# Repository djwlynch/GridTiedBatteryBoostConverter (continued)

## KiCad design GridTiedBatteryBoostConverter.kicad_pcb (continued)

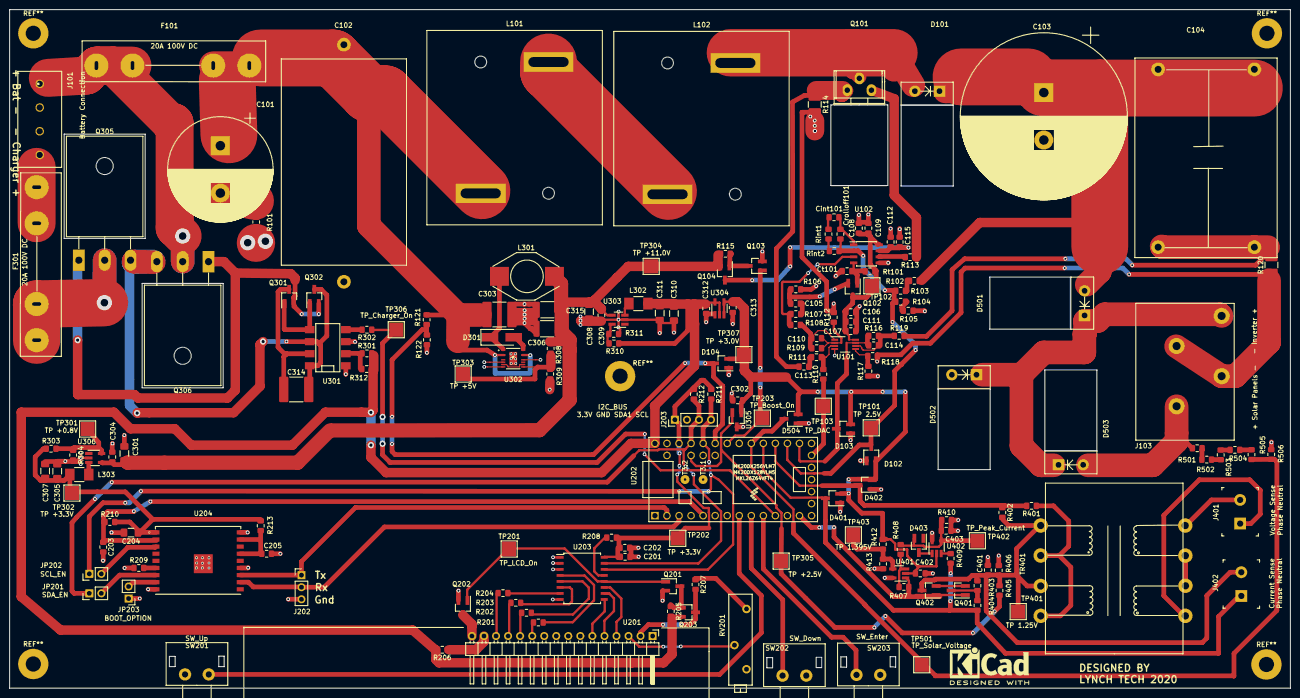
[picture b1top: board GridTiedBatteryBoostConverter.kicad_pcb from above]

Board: 2 copper layers, 270.1 x 143.1 mm, 183 parts (0 on the bottom side), 111 nets.

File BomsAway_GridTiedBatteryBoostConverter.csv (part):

Refs,Value,Footprint,Quantity,MFR,MPN,SPR,SPN
SW202,SW_Down,Buttons_Switches_ThroughHole_jl:SW_Tactile_SPST_Angled_FSM104,1,TE Connectivity ALCOSWITCH Switches,FSM104,digikey,450-1127-ND
SW203,SW_Enter,Buttons_Switches_ThroughHole_jl:SW_Tactile_SPST_Angled_FSM104,1,TE Connectivity ALCOSWITCH Switches,FSM104,digikey,450-1127-ND
SW201,SW_Up,Buttons_Switches_ThroughHole_jl:SW_Tactile_SPST_Angled_FSM104,1,TE Connectivity ALCOSWITCH Switches,FSM104,digikey,450-1127-ND
C402;C403;C309;C312;C304;C109;C112;C107;C202;C203;C205,0.1uF X7R 25V 10%,Capacitor_SMD:C_0805_2012Metric_Pad1.15x1.40mm_HandSolder,11,Samsung,CL21B104KACNNNC,digikey,1276-1099-1-ND
C302,0.47uF X7R 25V 10%,Capacitor_SMD:C_0805_2012Metric_Pad1.15x1.40mm_HandSolder,1,Samsung Electro-Mechanics,CL21B474KAFNNNE,digikey,1276-1074-1-ND
Cint101,0.56uF X7R 16V 10%,Capacitor_SMD:C_0805_2012Metric_Pad1.15x1.40mm_HandSolder,1,KEMET,C0805C564K4RACTU,dikikey,399-10074-1-ND
C105,100pF,Capacitor_SMD:C_0805_2012Metric_Pad1.15x1.40mm_HandSolder,1,KEMET,C0805C101JAGAC7800,digikey,399-15000-1-ND
C113,1nF,Capacitor_SMD:C_0805_2012Metric_Pad1.15x1.40mm_HandSolder,1,Yageo,CC0805KRX7R9BB102,digikey,311-1127-1-ND
C401;C313;C108;C114;C111;C106;C115;C201,1uF X7R 25V 10%,Capacitor_SMD:C_0805_2012Metric_Pad1.15x1.40mm_HandSolder,8,Wurth Elektronik,885012207078,digikey,732-7672-1-ND
Ct101,200pF C0G 2%,Capacitor_SMD:C_0805_2012Metric_Pad1.15x1.40mm_HandSolder,1,AVX Corporation,08051A201GAT2A,digikey,478-10384-1-ND
Crolloff101,68pF C0G 5%,Capacitor_SMD:C_0805_2012Metric_Pad1.15x1.40mm_HandSolder,1,Wurth Elektronik,885012007081,digikey,732-12227-1-ND
C110,6pF C0G,Capacitor_SMD:C_0805_2012Metric_Pad1.15x1.40mm_HandSolder,1,Yageo,CC0805CRNPO9BN6R0,digikey,311-4149-1-ND
C311;C310;C308;C307;C305;C301;C204,10uF X7R 25V 10%,Capacitor_SMD:C_1206_3216Metric_Pad1.42x1.75mm_HandSolder,7,Samsung Electro-Mechanics,CL31B106KAHNNNE,digikey,1276-1804-1-ND
C306;C315,33uF X7R 16V 20%,Capacitor_SMD:C_1812_4532Metric_Pad1.30x3.40mm_HandSolder,2,TDK Corporation,C4532X7R1C336M250KC,digikey,445-3924-1-ND
C303;C314,1uF X7R 250V 10%,Capacitor_SMD:C_2220_5650Metric_Pad1.97x5.40mm_HandSolder,2,TDK Corporation,C5750X7R2E105K230KA,digikey,445-2304-1-ND
C101,220uF ALUM 200V 905 mOhm 20%,Capacitor_THT:CP_Radial_D22.0mm_P10.00mm_SnapIn,1,Cornell Dubilier Electronics (CDE),SLP221M200A1P3,digikey,338-1478-ND
C103,470uF ALUM 400V 130mOhm 20%,Capacitor_THT:CP_Radial_D35.0mm_P10.00mm_SnapIn,1,KEMET,ELH477M400AT4AA,digikey,399-6073-ND
C102,15uF PP 250VDC 3.9mOhm,Capacitors_ThroughHole_jl:C_Axial_44mm_24.5mm_P50mm,1,KEMET,C4GADUD5150AA1J,digikey,399-13088-ND
C104,70uF PP Film 500V 2.1mOhm,Capacitors_ThroughHole_jl:C_RECT_4PIN_L42mm_W30mm_P37.5mm_P20.3mm,1,KEMET,C4AQLBW5700A3LK,digikey,399-17006-ND
F301;F101,Fuse Holder,Connect_jl:BellFuse_6.3mmX32mm_FC_102-22,2,Bel Fuse Inc.,FC-102-22,digikey,507-1702-ND
U201,LCD 2004A Right Angle Header 16 pin 2.54mm,Connect_jl:LCD2004_Pin_Header_Angled_1x16_Pitch2.54mm,1,Adam Tech,PH1RB-16-UA,digikey,2057-PH1RB-16-UA-ND
J101,Battery Connection,Connect_jl:PhoenixContact_1x4_P5mm,1,Phoenix Contact,1935792,digikey,277-14426-ND
J103,Solar Panels,Connect_jl:TerminalBlock_4way_P6.35mm_P9.5mm_Holes1.7mm,1,Phoenix Contact,1017516,digikey,277-17506-ND
D301,1A 150V 0.7V SMA,Diode_SMD:D_SMA_Handsoldering,1,Diodes Incorporated,SBR1U150SA-13,digikey,SBR1U150SA-13DICT-ND
D101,8A 200V 0.950V,Diodes_ThroughHole_jl:Diode_TO_220AC_Horizonal,1,Vishay Semiconductor Diodes Division,FES8DT-E3/45,digikey,FES8DT-E3/45GI-ND
D501;D503;D502,VS-20ETS12-M3 1200V 1V fwd@10A,Diodes_ThroughHole_jl:Diode_TO_220AC_Horizonal,3,Vishay Semiconductor Diodes Division,VS-20ETS12-M3,digikey,VS-20ETS12-M3-ND
U203,PCF8574ADWR,Housings_SOIC:SOIC-16W_7.5x10.3mm_Pitch1.27mm,1,Texas Instruments,PCF8574ADWR,digikey,296-13105-1-ND
U102,UCC2800DTR,Housings_SOIC:SOIC-8_3.9x4.9mm_Pitch1.27mm,1,Texas Instruments,UCC2800DTR,digikey,296-39529-1-ND
L302;L303,15uH 730mA Sat,Inductors_jl:Inductor_1210_HandSoldering,2,Taiyo Yuden,CBC3225T150KR,digikey,587-3066-1-ND
L301,150uH 610mA,Inductors_jl:Inductor_Bourns_PM3308,1,Bourns Inc.,PM3308-151M-RC,digikey,PM3308-151M-RCCT-ND
L101;L102,47uH 31A Sat 6.38m Ohm,Inductors_jl:Inductor_Wurth_7443763540470,2,Wurth Elektronik,7443763540470,digikey,732-13644-ND
U101,OPA2837IDGKR,Package_SO:VSSOP-8_3.0x3.0mm_P0.65mm,1,Texas Instruments,OPA2837IDGKR,digikey,296-49464-1-ND
U402,LMC7101BYM5-TR,Package_TO_SOT_SMD:SOT-23-5_HandSoldering,1,Microchip Technology,LMC7101BYM5-TR,digi-key,576-2575-1-ND
U401,MIC7211YM5-TR,Package_TO_SOT_SMD:SOT-23-5_HandSoldering,1,Microchip Technology,MIC7211YM5-TR,digi-key,576-1318-1-ND
U304,TLV70430DBVT,Package_TO_SOT_SMD:SOT-23-5_HandSoldering,1,Texas Instruments,TLV70430DBVT,digikey,296-32419-1-ND
U303;U306,TPS560200DBVR,Package_TO_SOT_SMD:SOT-23-5_HandSoldering,2,Texas Instruments,TPS560200DBVR,digikey,296-38559-1-ND
D401;D402;D403;D103;D102;D104;D504,BAT54S,Package_TO_SOT_SMD:SOT-23_Handsoldering,7,Toshiba Semiconductor and Storage,"TBAT54S,LM",digikey,TBAT54SLMCT-ND
Q301;Q102,BC847B-13-F,Package_TO_SOT_SMD:SOT-23_Handsoldering,2,Diodes Incorporated,BC847B-13-F,digikey,BC847B-13-FDICT-ND
Q302,BC856B-13-F,Package_TO_SOT_SMD:SOT-23_Handsoldering,1,Diodes Incorporated,BC856B-13-F,digikey,BC856B-13-FDICT-ND
U305,REF2925AIDBZT,Package_TO_SOT_SMD:SOT-23_Handsoldering,1,Texas Instruments,REF2925AIDBZT,digikey,296-13482-1-ND
Q104;Q203,SSM3J334R,Package_TO_SOT_SMD:SOT-23_Handsoldering,2,Toshiba Semiconductor and Storage,"SSM3J334R,LF",digikey,SSM3J334RLFCT-ND
Q401;Q402;Q103;Q201;Q202,SSM3K329R,Package_TO_SOT_SMD:SOT-23_Handsoldering,5,Toshiba Semiconductor and Storage,"SSM3K329R,LF",digikey,SSM3K329RLFCT-ND
JP203,BOOT_OPTION,Pin_Headers:Pin_Header_Straight_1x02_Pitch2.54mm,1,Sullins Connector Solutions,PREC002SAAN-RC,digikey,S1012EC-02-ND
JP202,SCL_EN,Pin_Headers:Pin_Header_Straight_1x02_Pitch2.54mm,1,Sullins Connector Solutions,PREC002SAAN-RC,digikey,S1012EC-02-ND
JP201,SDA_EN,Pin_Headers:Pin_Header_Straight_1x02_Pitch2.54mm,1,Sullins Connector Solutions,PREC002SAAN-RC,digikey,S1012EC-02-ND
J202,Conn_01x03_Female,Pin_Headers:Pin_Header_Straight_1x03_Pitch2.54mm,1,Sullins Connector Solutions,PREC003SAAN-RC,digikey,S1012EC-03-ND
J203,I2C_BUS,Pin_Headers:Pin_Header_Straight_1x04_Pitch2.54mm,1,Adam Tech,PH1-04-UA,digikey,2057-PH1-04-UA-ND
RV201,5K,Potentiometers:Potentiometer_Trimmer_Bourns_3006P,1,Bourns Inc,3006P-7-502LF,digikey,3006P-7-502LF-ND
U204,ESP-WROOM-02U,RF_Module_jl:MODULE_ESP-WROOM-02U,1,Espressif Systems,ESP-WROOM-02U,digikey,1904-1022-1-ND
R101,0R Ohms,Resistor_SMD:R_0805_2012Metric_Pad1.15x1.40mm_HandSolder,1,Stackpole Electronics Inc,RMCF0805ZT0R00,digikey,RMCF0805ZT0R00CT-ND
R412,1.15K 1%,Resistor_SMD:R_0805_2012Metric_Pad1.15x1.40mm_HandSolder,1,Yageo,RC0805FR-071K15L,digikey,311-1.15KCRCT-ND
R407,1.27K 1%,Resistor_SMD:R_0805_2012Metric_Pad1.15x1.40mm_HandSolder,1,Yageo,RC0805FR-071K27L,digikey,311-1.27KCRCT-ND
R104;Rint2;R122,1.5K 0.1%,Resistor_SMD:R_0805_2012Metric_Pad1.15x1.40mm_HandSolder,3,Panasonic Electronic Components,ERA-6AEB152V,digikey,P1.5KDACT-ND
R501;R502;R503;R504;R505;R205,100K 1%,Resistor_SMD:R_0805_2012Metric_Pad1.15x1.40mm_HandSolder,6,Yageo,RC0805FR-07100KL,digikey,311-100KCRCT-ND
R206,100R 1%,Resistor_SMD:R_0805_2012Metric_Pad1.15x1.40mm_HandSolder,1,Yageo,RC0805FR-07100RL,digikey,311-100CRCT-ND
R310;R121,105k 0.1%,Resistor_SMD:R_0805_2012Metric_Pad1.15x1.40mm_HandSolder,2,Panasonic Electronic Components,ERA-6AEB1053V,digikey,P105KDACT-ND
R110;R109;R117;R116,10K 0.1%,Resistor_SMD:R_0805_2012Metric_Pad1.15x1.40mm_HandSolder,4,Panasonic Electronic Components,ERA-6AEB103V,digikey,P10KDACT-ND
R113,10R 1%,Resistor_SMD:R_0805_2012Metric_Pad1.15x1.40mm_HandSolder,1,Yageo,RC0805FR-0710RL,digikey,311-10.0CRCT-ND
R107;R207;R210;R209;R213,15K 1%,Resistor_SMD:R_0805_2012Metric_Pad1.15x1.40mm_HandSolder,5,TE Connectivity Passive Product,CRGCQ0805F15K,digikey,A129763CT-ND
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
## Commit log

2020-07-29 Inital commit of GridTiedBatteryBoostConverter, a bit off a mess but I should have a backupgit status
2020-07-30 started routing backing up tonnes of changes,2.048V reference changed to 2.5V ref, to match ucc2800, cos to change to a version with a 2V feedback, would require me to update the Oscillator cap and r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
2020-07-31 Almost finished the routing, an other backup commit git add *
2020-07-31 Finish routing finally
2020-07-31 fixed a few DRC errors, introduced error by adding edge.cuts to the buttons footprint, now warns board outline not complete. 3d wont completely render also because of this.
2020-07-31 added mounting holes, should have done that sort of thing right at start.
2020-07-31 added testpoints
2020-07-31 changed Buttons_Switches_ThroughHole_jl:SW_Tactile_SPST_Angled_FSM104 foot print
2020-07-31 regenerated BOM, for the first time after new layout with wifi etc.
2020-08-01 Consolidated a lot of part values that were the same part but not detected the same by Boms_away BOM editor because of subtle differences in how I specified the values. Added Digi-key part numbers to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
2020-08-02 change a few compoents foot prints for SOT23 to SOT23-Handsoldered, and SOT23-5 to SOT23-5-Handsoldered
2020-08-02 Finished adding digi key part numbers, for now git add *
2020-08-03 added thermal via of .3 drill size and .6, I have read the recomenned size is .25 drill but the smallest JLCPCB do for double sided boards is .3
2020-08-03 regenerated built in kicad BOM Tool, since adding all the digi-key parts with bomsaway.py
2020-08-03 Generated BOM using bomsaway.py
2020-08-04 change Fuse details to a graphic note, and change the Fuse supply details to refer to the fuse holder, not the fuse it self. Also rerouted the charger input using 8mm trace width were possible.
2020-08-04 added labels for the battery, charger, inverter and solar panels + - connections.
2020-08-05 Started making progress towards people being able to clone the the repository without getting messages about missing librarys needing rescue. started simplifying where some component librarys are loc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
2020-08-06 modified the symbol librarys and footprint librarys to use the project specific librarys instead of my global table making it easier for people to clone and use the project, with out missing librarie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
2020-08-06 Changed the ground plane copper fill zone to have a default clearance of 1.25mm to allow for up to 170V for external conductors uncoated according to IPC 2221B Table 6-1. Then the 500V connectors tra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
2020-08-07 change how the current sense traces attach to the average output current sense resistor R120, they are now at right angles to the current sense resistor and attach directly to it.
2020-08-07 further improved routing of sense trace to current sense resistor R120
2020-08-07 added the results from CalcBoostComponents(89.6, 102.2, 160, 100, 1000, 250000, .01, .01,.80) in file ComponetCalculations.txt
2020-08-08 Replaced TK32A12N1,S4X TO-220 Toshiba transistors that were use for turning the charger on and off, with a pair of IRFP4321PBF's from Infinion, in a TO-247AC package. The reson for the change was thi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
2020-08-08 Change footprint for the main switching FET to have a bent drain to achieve trace width and clearance requirements. Fixed a pin numbering miss alignment between schematic and footprint for the isolat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
2020-08-10 Improved clearance of Vin into U302 as good as the package will allow. Also reduced clearance around the Teesy to 0.5mm, because I notice one for the grounds was not connected.
2020-08-11 The Wurth main inductors turned up today, and I spotted a stuff up with the footprint layout, pins are in the right spot, but the body outline is x-y switched, so the 2 inductors would not fit, so fi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
2020-08-14 Found that my local updates of Kicad footprint librarys, had changed the names of resistor and capacitor footprints, so I updated all these footprint names. Added circuit to measure the Vin via pin 2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
2020-08-16 Added a dedicated fuse for the charger connection. Lowered the fuses from 25A to 20A after looking more closely at the data sheet. Charger is 19.5A atmost and Battery current draw at 80% efficency, 8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
2020-08-17 Replaced the 3.5mm headphone jack which was used as the current transformer input, I thought due to the dangerous voltages that can be developed if it is connected to the mains without being pluged i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
2020-08-17 Added voltage divider network and input protection to measure, the Solar input voltage, I decided this would be usefull in the cases where the solar is producing voltage over 160V, but the house is s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
2020-08-17 Regenerated BOM after adding Solar Voltage measuring circuit, and updated TestPoint footprint that was missed in earler commit.
2020-08-22 Added Auto Range circuit to the Mains Current Sense, this will give close to 1W resolution on the mains measurment in the range 0-2000W vs about 6.6W resolution. Updated the BOM, which I think caused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
2020-08-22 Added Current_Range_Hi_Lo signal from the Mains Current Sense circuit to the Micro so we can tell what range we are operating on.
2020-08-22 Routed recent auto mains current ranging circuit.
2020-08-23 Added extra FET in Current sense Auto Ranging circuit to stop the conduction of the body diode of the single FET on the negative half of the mains cycle. Also change the Values of all the TestPoints 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
2020-08-24 increased some trace sizes, moved some Front mask items, and generated the Gerber files, and submited order to jlcpcb, only order 1 oz copper but should be 2 oz due the the 20A charging part of the c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
2021-02-19 added scope captures to diagnose lower power output ~11Watts.
